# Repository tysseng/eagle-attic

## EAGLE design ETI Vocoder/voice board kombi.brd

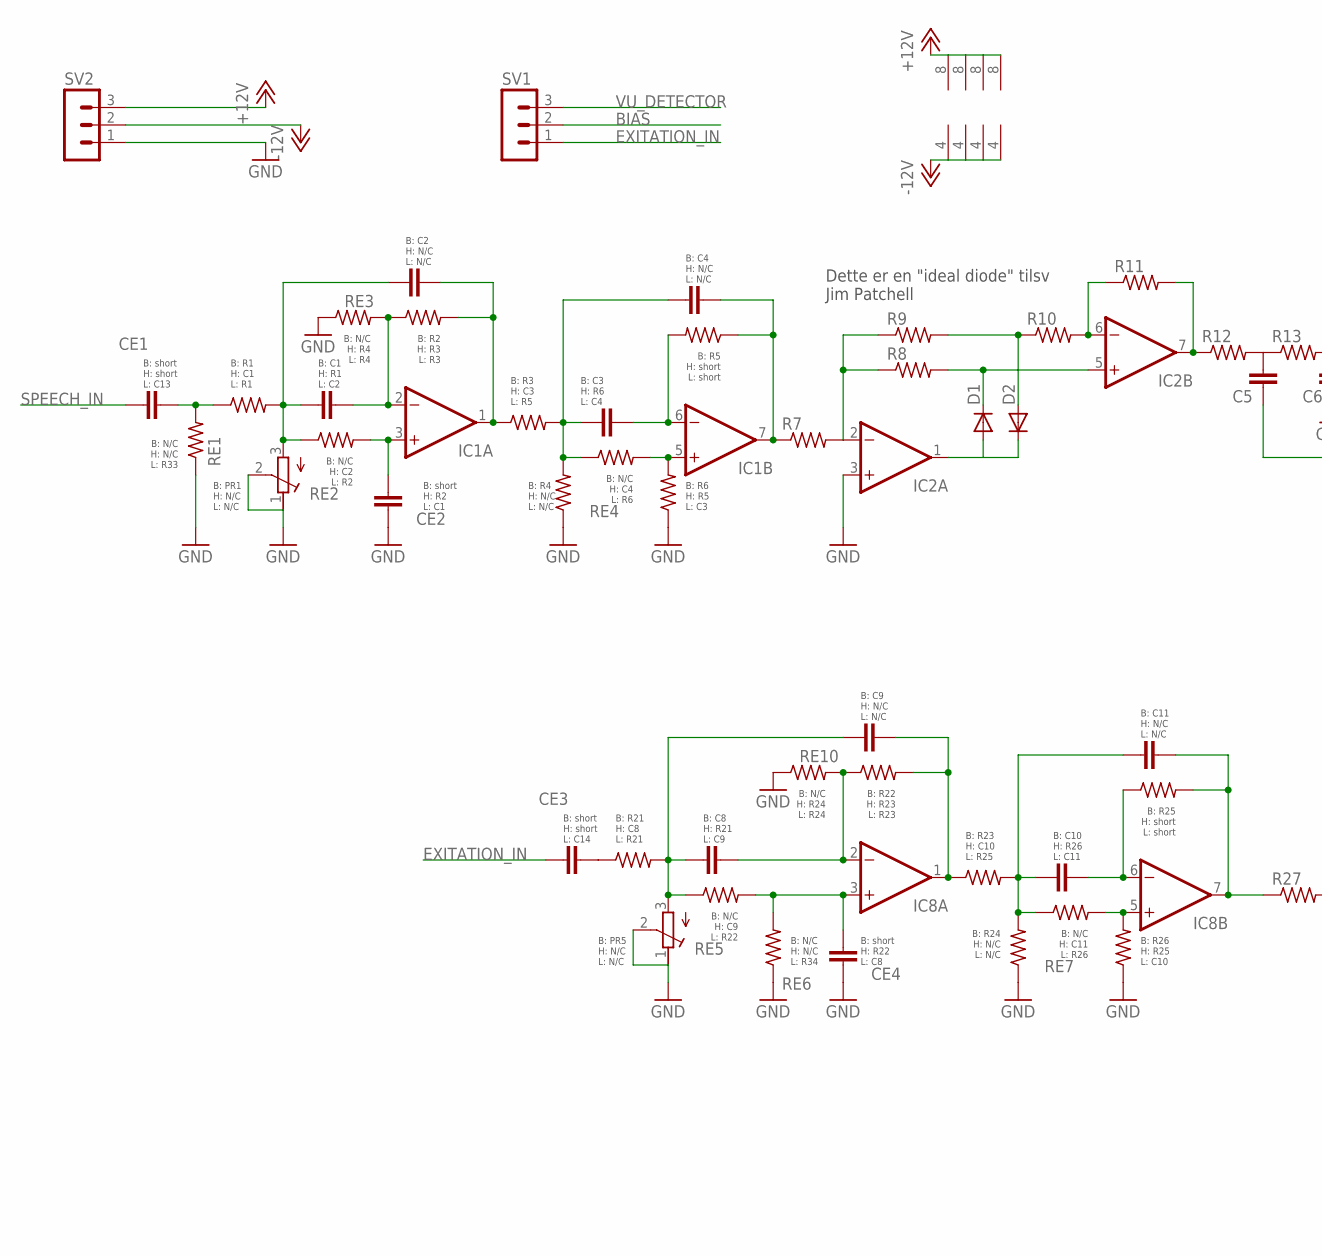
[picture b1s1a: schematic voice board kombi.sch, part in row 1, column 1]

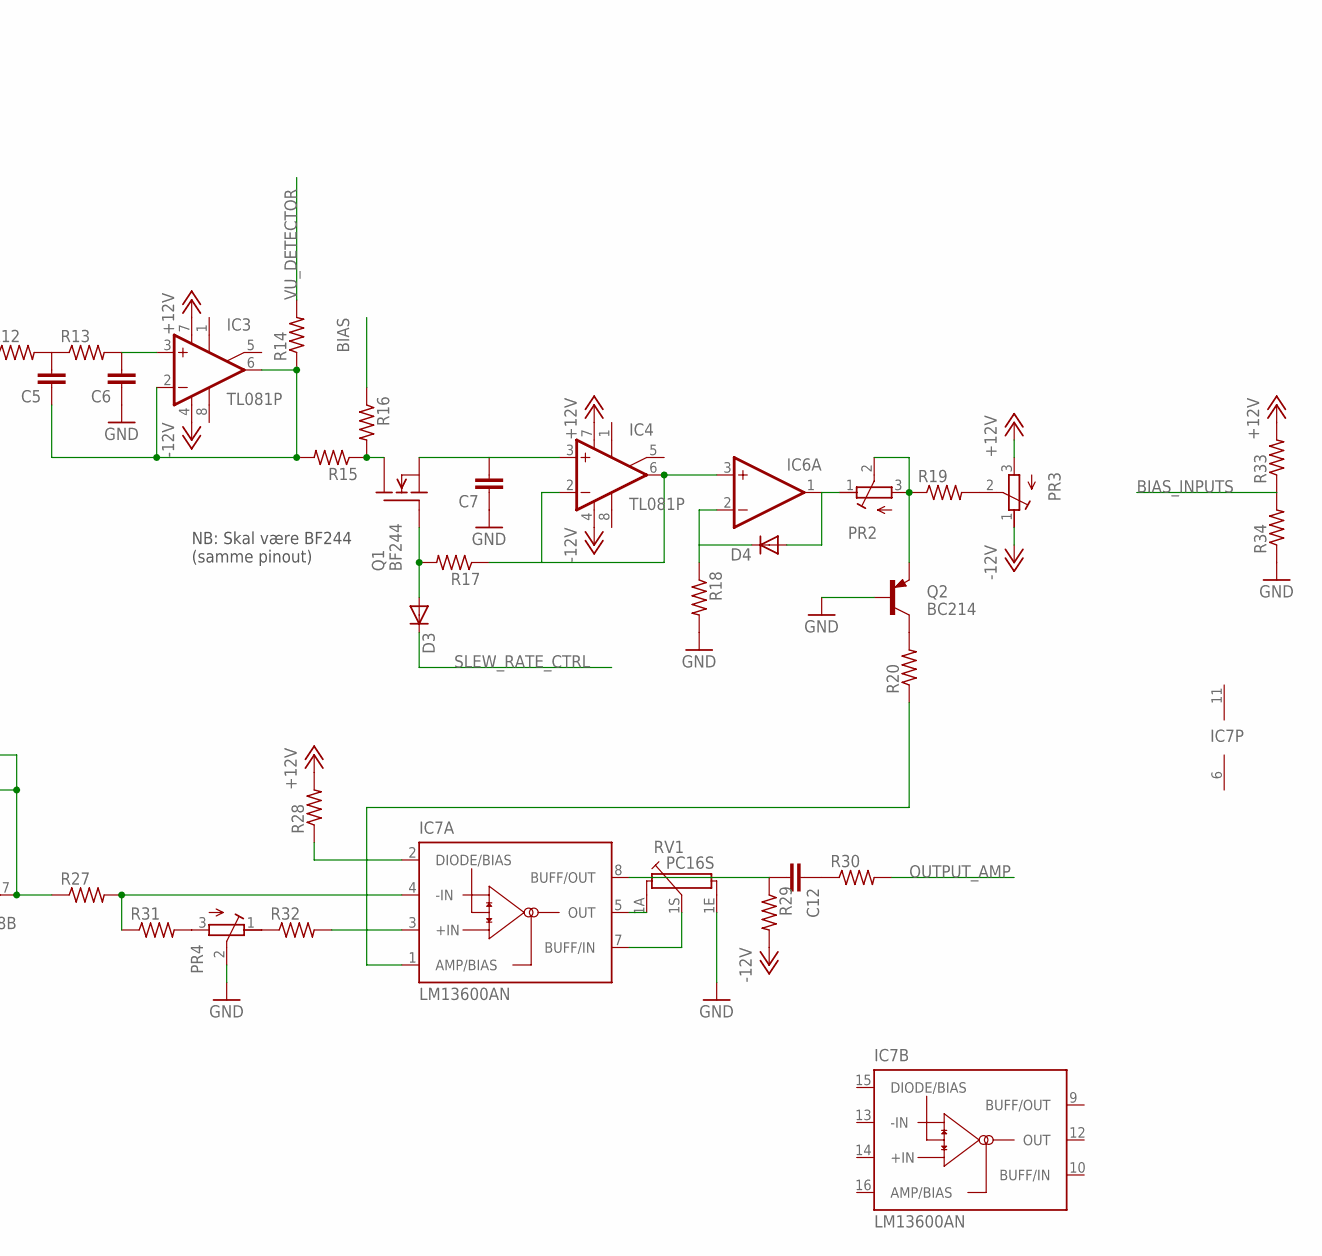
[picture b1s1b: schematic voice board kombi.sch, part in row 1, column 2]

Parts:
C1, C2, C3, C4, C5, C6, C7, C8, C9, C10, C11, C12: C-EU050-025X075; C050-025X075
CE1, CE2, CE3, CE4: C-EU050-025X075; C050-025X075
D1, D2, D3, D4: DIODE-D-5; D-5
IC1, IC2, IC6, IC8: TL072P; DIL08
IC3, IC4: TL081P; DIL08
IC7: LM13600AN; DIL16
PR1, PR2, PR3, PR4, PR5: R-TRIMMT93XA; RTRIMT93XA
Q1: BF244; TO-92
Q2: BC214; TO92
R1, R2, R3, R4, R5, R6, R7, R8, R9, R10, R11, R12, R13, R14, R15, R16, R17, R18, R19, R20, R21, R22, R23, R24, R25, R26, R27, R28, R29, R30, R31, R32, R33, R34: R-US_0207/7; 0207/7
RE1, RE2, RE3, RE4, RE5, RE6, RE7, RE10: R-US_0207/7; 0207/7
RV1: PC16S
SV1, SV2: MA03-1

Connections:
+12V: IC1.8 (V+), IC2.8 (V+), IC3.7 (V+), IC4.7 (V+), IC6.8 (V+), IC8.8 (V+), PR3.3 (A), R28.2, R33.2, SV2.3
-12V: IC1.4 (V-), IC2.4 (V-), IC3.4 (V-), IC4.4 (V-), IC6.4 (V-), IC8.4 (V-), PR3.1 (E), R29.2, SV2.2
BIAS: R16.1, SV1.2
BIAS_INPUTS: R33.1, R34.2
EXITATION_IN: CE3.1, SV1.1
GND: C6.1, C7.1, CE2.1, CE4.1, IC2.3 (+IN), PR1.1 (E), PR1.2 (S), PR4.2 (S), PR5.1 (E), PR5.2 (S), Q2.2 (B), R4.1, R6.1, R18.2, R24.1, R26.1, R34.1, RE1.1, RE3.1, RE6.1, RE10.1, RV1.1E, SV2.1
unnamed: C1.2, IC1.2 (-IN), R2.1, RE3.2
unnamed: C1.1, C2.1, PR1.3 (A), R1.2, RE2.1
unnamed: C2.2, IC1.1 (OUT), R2.2, R3.1
unnamed: IC2.2 (-IN), R7.2, R8.1, R9.1
unnamed: C3.1, C4.1, R3.2, R4.2, RE4.1
unnamed: C3.2, IC1.6 (-IN), R5.2
unnamed: IC1.5 (+IN), R6.2, RE4.2
unnamed: C4.2, IC1.7 (OUT), R5.1, R7.1
unnamed: D1.C, IC2.5 (+IN), R8.2
unnamed: D1.A, D2.C, IC2.1 (OUT)
unnamed: D2.A, R9.2, R10.1
unnamed: IC2.6 (-IN), R10.2, R11.1
unnamed: IC2.7 (OUT), R11.2, R12.1
unnamed: C5.2, R12.2, R13.1
unnamed: C5.1, IC3.2 (-IN), IC3.6 (OUT), R14.1, R15.2
unnamed: C6.2, IC3.3 (+IN), R13.2
unnamed: Q1.3 (D), R15.1, R16.2
unnamed: C7.2, IC4.3 (+IN), Q1.1 (S)
unnamed: D3.A, Q1.2 (G), R17.2
unnamed: IC4.2 (-IN), IC4.6 (OUT), IC6.3 (+IN), R17.1
unnamed: D4.C, IC6.2 (-IN), R18.1
unnamed: D4.A, IC6.1 (OUT), PR2.1 (E)
unnamed: PR2.2 (S), PR2.3 (A), Q2.1 (E), R19.1
unnamed: PR3.2 (S), R19.2
unnamed: Q2.3 (C), R20.2
unnamed: PR4.3 (A), R31.2
unnamed: C8.2, C9.2, PR5.3 (A), R21.2, RE5.1
unnamed: C10.2, C11.2, R23.2, R24.2, RE7.1
unnamed: C8.1, IC8.2 (-IN), R22.1, RE10.2
unnamed: C9.1, IC8.1 (OUT), R22.2, R23.1
unnamed: C10.1, IC8.6 (-IN), R25.1
unnamed: IC8.5 (+IN), R26.2, RE7.2
unnamed: C12.2, IC7.8 (BUFF/OUT), R29.1
unnamed: C12.1, R30.1
unnamed: C11.1, IC8.7 (OUT), R25.2, R27.1
unnamed: PR4.1 (E), R32.1
unnamed: IC7.3 (+IN), R32.2
unnamed: IC7.2 (DIODE/BIAS), R28.1
unnamed: IC7.4 (-IN), R27.2, R31.1
unnamed: IC7.1 (AMP/BIAS), R20.1
unnamed: IC7.5 (OUT), RV1.1A
unnamed: IC7.7 (BUFF/IN), RV1.1S
unnamed: CE1.2, R1.1, RE1.2
unnamed: CE2.2, IC1.3 (+IN), RE2.2
unnamed: CE3.2, R21.1
unnamed: CE4.2, IC8.3 (+IN), RE5.2, RE6.2
OUTPUT_AMP: R30.2
SLEW_RATE_CTRL: D3.C
SPEECH_IN: CE1.1
V+: IC7.11 (V+)
V-: IC7.6 (V-)
VU_DETECTOR: R14.2, SV1.3

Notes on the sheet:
NB: Skal være BF244 (samme pinout)
Dette er en "ideal diode" tilsv Jim Patchell
B: short H: short L: C13
B: R1 H: C1 L: R1
B: PR1 H: N/C L: N/C
B: C1 H: R1 L: C2
B: C2 H: N/C L: N/C
B: C4 H: N/C L: N/C
B: R2 H: R3 L: R3
B: R3 H: C3 L: R5
B: R4 H: N/C L: N/C
B: C3 H: R6 L: C4
B: R6 H: R5 L: C3
B: R5 H: short L: short
B: N/C H: R4 L: R4
B: short H: R2 L: C1
B: N/C H: C2 L: R2
B: N/C H: N/C L: R33
B: short H: short L: C14
B: R21 H: C8 L: R21
B: C8 H: R21 L: C9
B: R22 H: R23 L: R23
B: C9 H: N/C L: N/C
B: C10 H: R26 L: C11
B: R23 H: C10 L: R25
B: N/C H: N/C L: R34
B: R24 H: N/C L: N/C
B: R26 H: R25 L: C10
B: C11 H: N/C L: N/C
B: R25 H: short L: short
B: N/C H: C9 L: R22
B: short H: R22 L: C8
B: N/C H: C4 L: R6
B: N/C H: C11 L: R26
B: PR5 H: N/C L: N/C
B: N/C H: R24 L: R24

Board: 2 copper layers, 79 parts (0 on the bottom side), 53 nets, no tracks yet.

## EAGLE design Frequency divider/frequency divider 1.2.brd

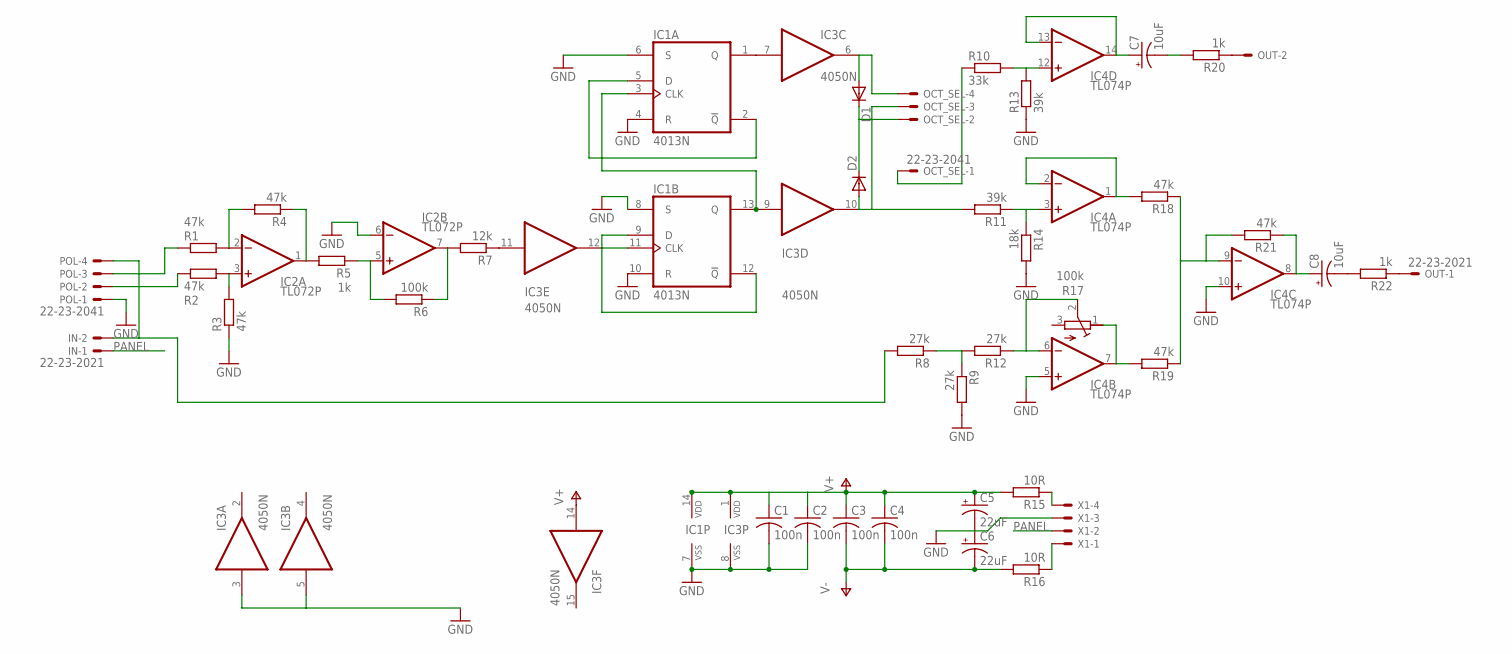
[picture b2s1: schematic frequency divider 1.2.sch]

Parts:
C1, C2, C3, C4: 100n; C025-024X044
C5, C6: 22uF; E2,5-5
C7, C8: 10uF; E2,5-5
D1, D2: DIODE-D-5; D-5
IC1: 4013N; DIL14
IC2: TL072P; DIL08
IC3: 4050N; DIL16
IC4: TL074P; DIL14
IN: 22-23-2021
OCT_SEL: 22-23-2041
OUT: 22-23-2021
POL: 22-23-2041
R1, R2, R3, R4, R18, R19, R21: 47k; 0204/7
R5, R20, R22: 1k; 0204/7
R6: 100k; 0204/7
R7: 12k; 0204/7
R8, R9, R12: 27k; 0204/7
R10: 33k; 0204/7
R11, R13: 39k; 0204/7
R14: 18k; 0204/7
R15, R16: 10R; 0204/7
R17: 100k; RTRIMT93YA
X1: KK-156-4

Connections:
GND: C1.2, C2.2, C5.-, C6.+, IC1.4 (R), IC1.6 (S), IC1.7 (VSS), IC1.8 (S), IC1.10 (R), IC2.6 (-IN), IC3.3 (I), IC3.5 (I), IC3.8 (VSS), IC4.5 (+IN), IC4.10 (+IN), POL.1, R3.1, R9.2, R13.1, R14.2, X1.3
unnamed: C7.-, R20.2
unnamed: C8.-, R22.2
unnamed: IC2.2 (-IN), R1.2, R4.2
unnamed: IC2.3 (+IN), R2.2, R3.2
unnamed: IC2.1 (OUT), R4.1, R5.2
unnamed: IC1.3 (CLK), IC1.13 (Q), IC3.9 (I)
unnamed: IC2.5 (+IN), R5.1, R6.2
unnamed: IC2.7 (OUT), R6.1, R7.2
unnamed: IC3.11 (I), R7.1
unnamed: IC1.11 (CLK), IC3.12 (O)
unnamed: IC1.9 (D), IC1.12 (!Q)
unnamed: D2.A, IC3.10 (O), OCT_SEL.3, R11.2
unnamed: IC4.3 (+IN), R11.1, R14.1
unnamed: IC4.12 (+IN), R10.2, R13.2
unnamed: C7.+, IC4.13 (-IN), IC4.14 (OUT)
unnamed: IC4.1 (OUT), IC4.2 (-IN), R18.2
unnamed: IC4.6 (-IN), R12.1, R17.2 (S)
unnamed: IC4.7 (OUT), R17.1 (A), R19.2
unnamed: R15.1, X1.4
unnamed: R8.1, R9.1, R12.2
unnamed: IC4.9 (-IN), R18.1, R19.1, R21.2
unnamed: C8.+, IC4.8 (OUT), R21.1
unnamed: R16.1, X1.1
unnamed: OUT.2, R20.1
unnamed: IN.2, POL.4, R8.2
unnamed: OUT.1, R22.1
unnamed: POL.2, R2.1
unnamed: POL.3, R1.1
unnamed: IC1.2 (!Q), IC1.5 (D)
unnamed: IC1.1 (Q), IC3.7 (I)
unnamed: D1.A, IC3.6 (O), OCT_SEL.4
unnamed: D1.C, D2.C, OCT_SEL.2
unnamed: OCT_SEL.1, R10.1
PANEL: IN.1, X1.2
V+: C1.1, C2.1, C3.1, C4.1, C5.+, IC1.14 (VDD), IC2.8 (V+), IC3.1 (VDD), IC3.14 (I), IC4.4 (V+), R15.2
V-: C3.2, C4.2, C6.-, IC2.4 (V-), IC4.11 (V-), R16.2

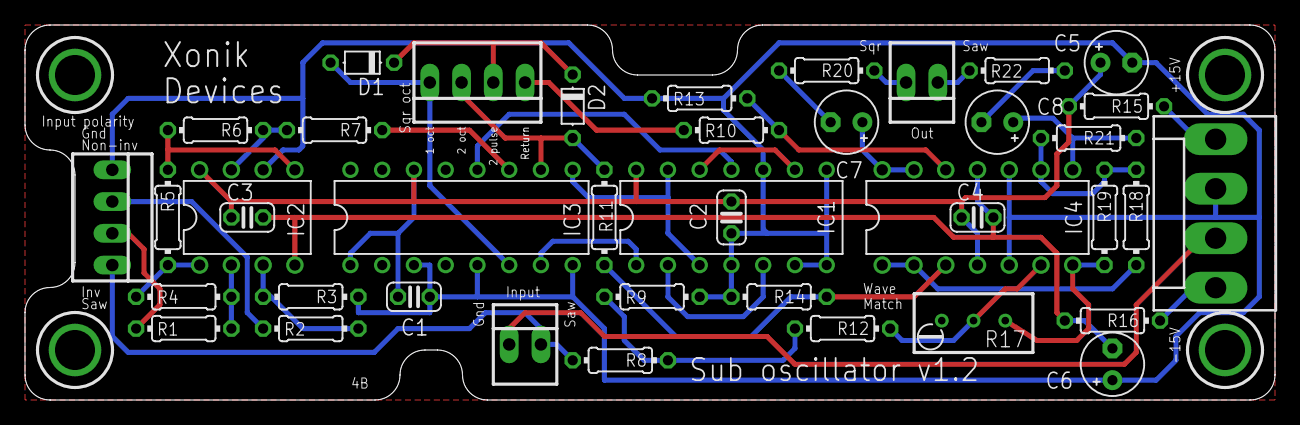
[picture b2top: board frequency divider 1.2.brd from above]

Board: 2 copper layers, 100.0 x 30.0 mm, 41 parts (0 on the bottom side), 37 nets.

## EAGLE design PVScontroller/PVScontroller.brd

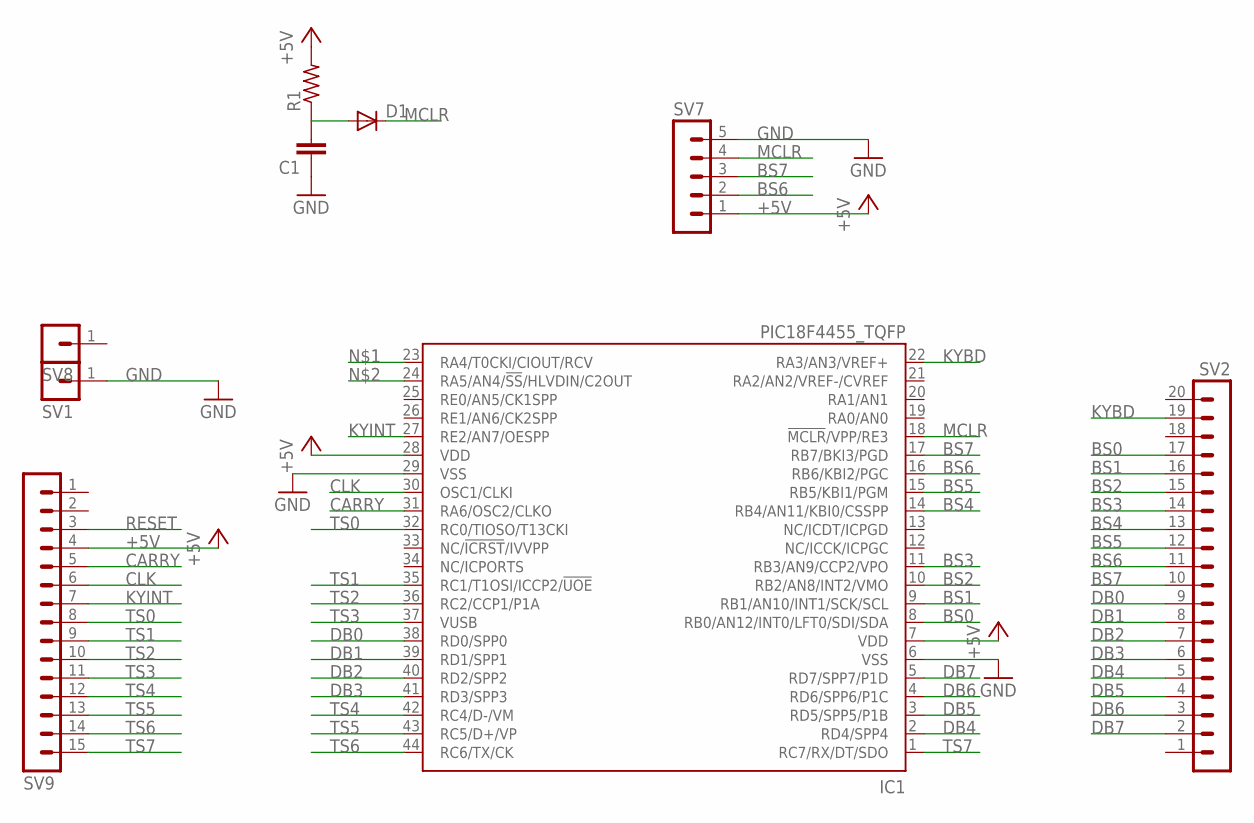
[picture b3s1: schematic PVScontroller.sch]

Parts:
C1: C-EUC0805; C0805
D1: DIODE-SOD80C; SOD80C
IC1: PIC18F4455_TQFP; TQFP44
R1: R-US_R0805; R0805
SV1, SV8: MA01-1
SV2: MA20-1
SV7: MA05-1
SV9: MA15-1

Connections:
+5V: IC1.7 (VDD), IC1.28 (VDD), R1.2, SV7.1, SV9.4
BS0: IC1.8 (RB0/AN12/INT0/LFT0/SDI/SDA), SV2.17
BS1: IC1.9 (RB1/AN10/INT1/SCK/SCL), SV2.16
BS2: IC1.10 (RB2/AN8/INT2/VMO), SV2.15
BS3: IC1.11 (RB3/AN9/CCP2/VPO), SV2.14
BS4: IC1.14 (RB4/AN11/KBI0/CSSPP), SV2.13
BS5: IC1.15 (RB5/KBI1/PGM), SV2.12
BS6: IC1.16 (RB6/KBI2/PGC), SV2.11, SV7.2
BS7: IC1.17 (RB7/BKI3/PGD), SV2.10, SV7.3
CARRY: IC1.31 (RA6/OSC2/CLKO), SV9.5
CLK: IC1.30 (OSC1/CLKI), SV9.6
DB0: IC1.38 (RD0/SPP0), SV2.9
DB1: IC1.39 (RD1/SPP1), SV2.8
DB2: IC1.40 (RD2/SPP2), SV2.7
DB3: IC1.41 (RD3/SPP3), SV2.6
DB4: IC1.2 (RD4/SPP4), SV2.5
DB5: IC1.3 (RD5/SPP5/P1B), SV2.4
DB6: IC1.4 (RD6/SPP6/P1C), SV2.3
DB7: IC1.5 (RD7/SPP7/P1D), SV2.2
GND: C1.1, IC1.6 (VSS), IC1.29 (VSS), SV1.1, SV7.5
KYBD: IC1.22 (RA3/AN3/VREF+), SV2.19
KYINT: IC1.27 (RE2/AN7/OESPP), SV9.7
MCLR: D1.C, IC1.18 (!MCLR!/VPP/RE3), SV7.4
unnamed: C1.2, D1.A, R1.1
RESET: SV9.3
TS0: IC1.32 (RC0/TIOSO/T13CKI), SV9.8
TS1: IC1.35 (RC1/T1OSI/ICCP2/!UOE), SV9.9
TS2: IC1.36 (RC2/CCP1/P1A), SV9.10
TS3: IC1.37 (VUSB), SV9.11
TS4: IC1.42 (RC4/D-/VM), SV9.12
TS5: IC1.43 (RC5/D+/VP), SV9.13
TS6: IC1.44 (RC6/TX/CK), SV9.14
TS7: IC1.1 (RC7/RX/DT/SDO), SV9.15

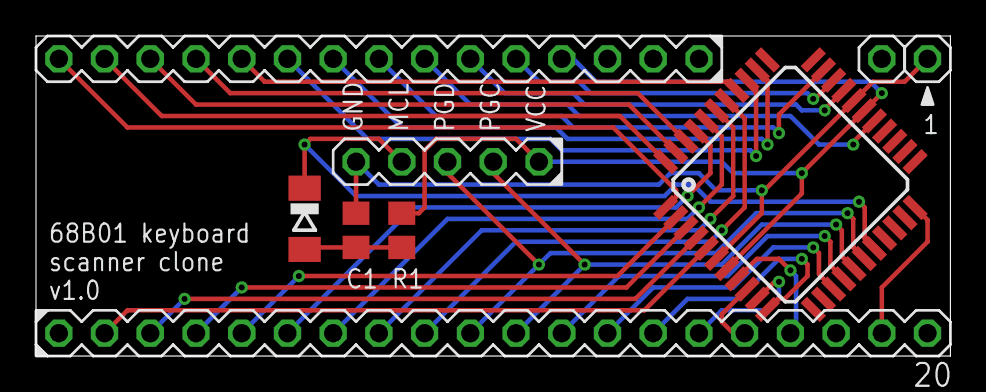
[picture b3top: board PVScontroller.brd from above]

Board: 2 copper layers, 50.8 x 17.8 mm, 9 parts (0 on the bottom side), 32 nets.
